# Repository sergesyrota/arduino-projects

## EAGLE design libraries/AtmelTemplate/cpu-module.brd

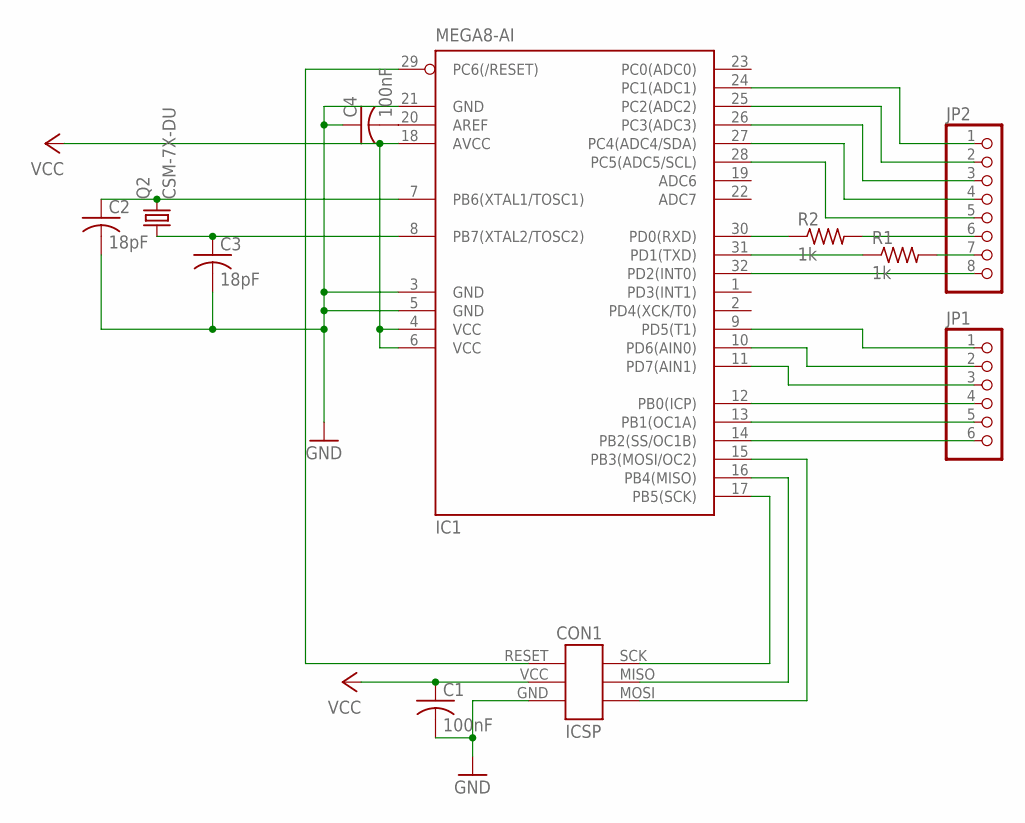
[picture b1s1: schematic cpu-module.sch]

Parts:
C1, C4: 100nF; C0603K
C2, C3: 18pF; C0805
CON1: ICSP-HEADER
IC1: MEGA8-AI; TQFP32-08
JP1: PINHD-1X6B; 1X06-BIG
JP2: PINHD-1X8BIG; 1X08-BIG
Q2: CSM-7X-DU
R1, R2: 1k; R0603

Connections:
GND: C1.2, C2.2, C3.2, C4.1, CON1.GND, IC1.3 (GND), IC1.5 (GND), IC1.21 (GND)
unnamed: C2.1, IC1.7 (PB6(XTAL1/TOSC1)), Q2.2
unnamed: C3.1, IC1.8 (PB7(XTAL2/TOSC2)), Q2.1
unnamed: C4.2, IC1.20 (AREF)
unnamed: CON1.SCK, IC1.17 (PB5(SCK))
unnamed: CON1.MISO, IC1.16 (PB4(MISO))
unnamed: CON1.MOSI, IC1.15 (PB3(MOSI/OC2))
unnamed: IC1.30 (PD0(RXD)), R2.1
unnamed: JP2.7, R1.2
unnamed: IC1.31 (PD1(TXD)), R1.1
unnamed: IC1.32 (PD2(INT0)), JP2.8
unnamed: IC1.24 (PC1(ADC1)), JP2.1
unnamed: CON1.RESET, IC1.29 (PC6(/RESET))
unnamed: IC1.25 (PC2(ADC2)), JP2.2
unnamed: IC1.26 (PC3(ADC3)), JP2.3
unnamed: IC1.27 (PC4(ADC4/SDA)), JP2.4
unnamed: IC1.28 (PC5(ADC5/SCL)), JP2.5
unnamed: IC1.14 (PB2(SS/OC1B)), JP1.6
unnamed: IC1.13 (PB1(OC1A)), JP1.5
unnamed: IC1.12 (PB0(ICP)), JP1.4
unnamed: IC1.11 (PD7(AIN1)), JP1.3
unnamed: IC1.10 (PD6(AIN0)), JP1.2
unnamed: IC1.9 (PD5(T1)), JP1.1
unnamed: JP2.6, R2.2
VCC: C1.1, CON1.VCC (+5V), IC1.4 (VCC), IC1.6 (VCC), IC1.18 (AVCC)

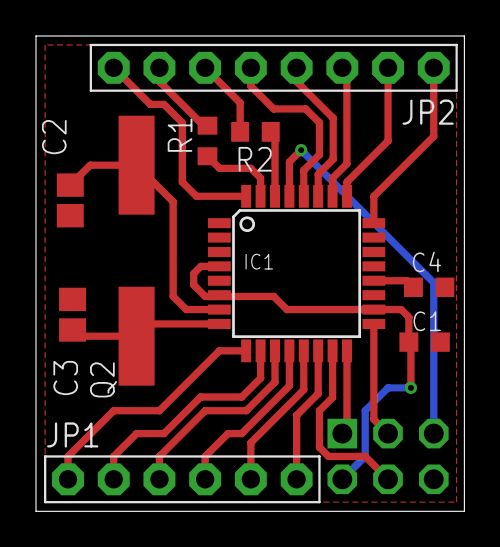
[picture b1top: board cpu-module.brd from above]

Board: 2 copper layers, 23.8 x 26.4 mm, 11 parts (1 on the bottom side), 25 nets.

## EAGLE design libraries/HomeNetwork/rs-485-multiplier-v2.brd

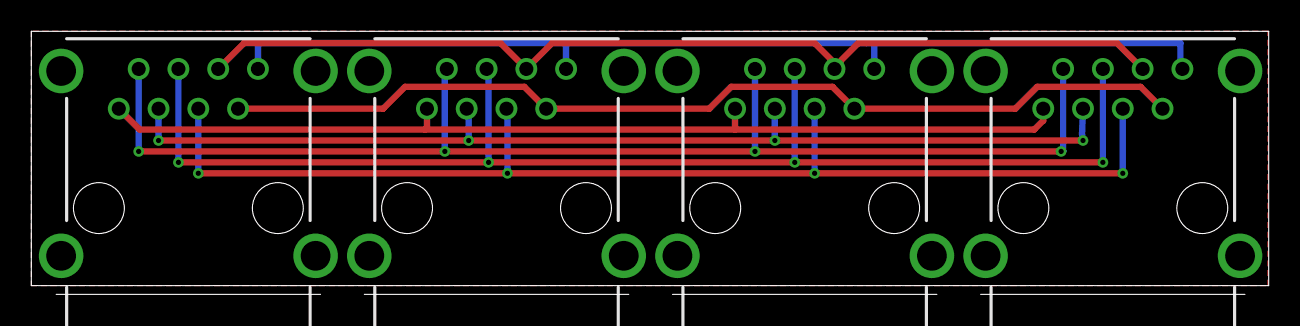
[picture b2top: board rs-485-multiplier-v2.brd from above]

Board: 2 copper layers, 79.0 x 16.8 mm, 4 parts (0 on the bottom side), 8 nets.

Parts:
X1, X2, X3, X4: RJ45-6L21-B; RJ45-SHIELD1

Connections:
unnamed: X1.1, X2.1, X3.1, X4.1
unnamed: X1.2, X2.2, X3.2, X4.2
unnamed: X1.3, X2.3, X3.3, X4.3
unnamed: X1.4, X2.4, X3.4, X4.4
unnamed: X1.5, X2.5, X3.5, X4.5
unnamed: X1.6, X2.6, X3.6, X4.6
unnamed: X1.7, X2.7, X3.7, X4.7
unnamed: X1.8, X2.8, X3.8, X4.8

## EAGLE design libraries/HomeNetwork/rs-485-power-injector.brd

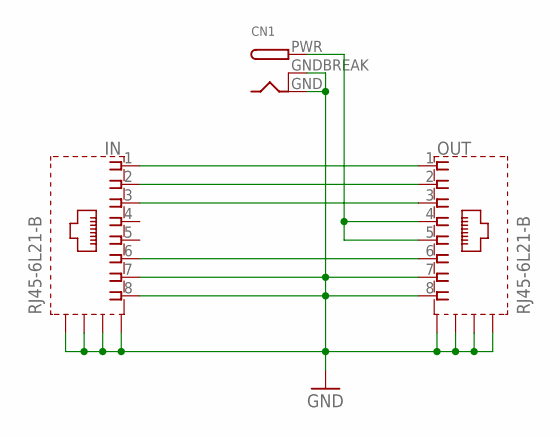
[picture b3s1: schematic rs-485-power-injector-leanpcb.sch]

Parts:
CN1: DCBARRELPTH; DCJACK_2MM_PTH
IN: RJ45-6L21-B; RJ45-SHIELD1
OUT: RJ45-6L21-B; RJ45-SHIELD1

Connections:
GND: CN1.GND, CN1.GNDBREAK, IN.7, IN.8, IN.S1 (S), IN.S2 (S), IN.S3 (S), IN.S4 (S), OUT.7, OUT.8, OUT.S1 (S), OUT.S2 (S), OUT.S3 (S), OUT.S4 (S)
unnamed: IN.1, OUT.1
unnamed: IN.2, OUT.2
unnamed: IN.3, OUT.3
unnamed: IN.6, OUT.6
unnamed: CN1.PWR, OUT.4, OUT.5

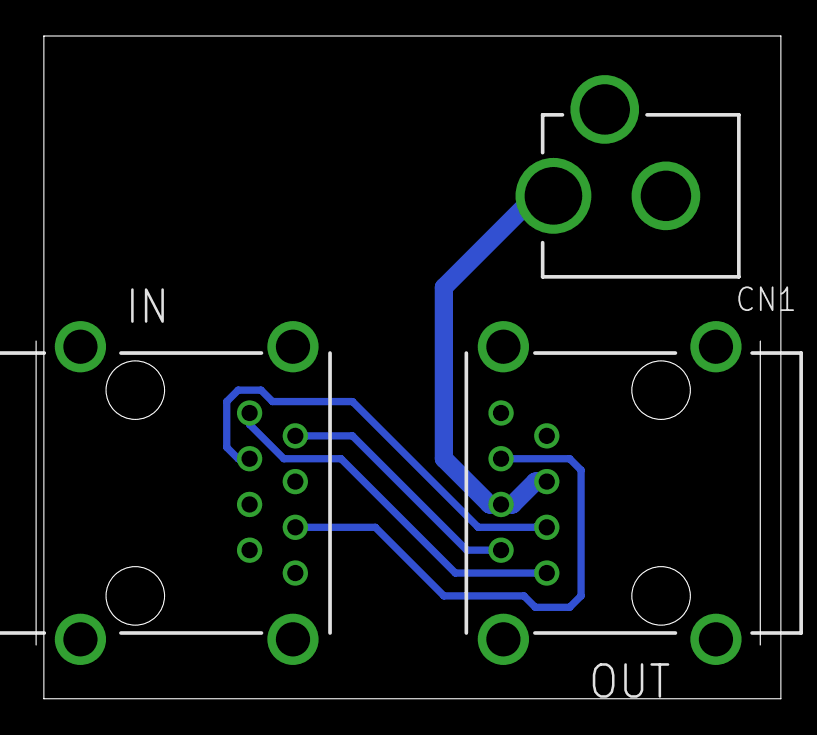
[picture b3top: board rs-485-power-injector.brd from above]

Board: 2 copper layers, 40.9 x 36.8 mm, 3 parts (0 on the bottom side), 6 nets.

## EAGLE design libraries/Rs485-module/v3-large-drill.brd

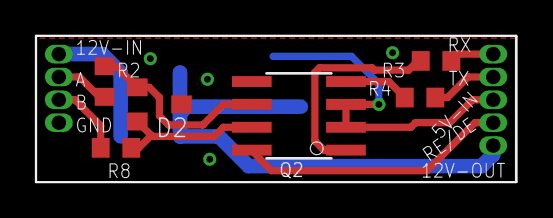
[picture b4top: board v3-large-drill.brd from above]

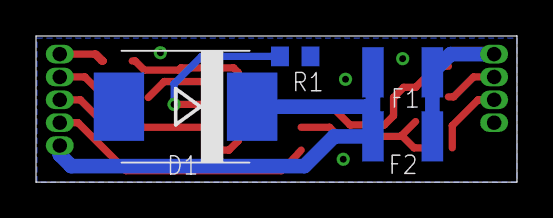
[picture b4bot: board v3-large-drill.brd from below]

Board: 2 copper layers, 26.7 x 8.1 mm, 11 parts (4 on the bottom side), 13 nets.

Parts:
D1: SMC
D2: SM712SOT23-3-SHRINKED; SOT23-3-SHRINKED
F1, F2: PTC-1210; 1210
Q1: RS485-ADAPTER0.05-CONNECTOR; RS485-ADAPTOR-05
Q2: MAX481SO08; SO08
R1: 50k; R0603
R2, R8: 100; R0603
R3, R4: 1k; R0603

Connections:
12V-IN: F1.2, F2.2, Q1.12V-IN
A: Q1.A, R2.2
B: Q1.B, R8.2
GND: D1.A, D2.3, Q1.GND, Q2.5, R1.1
unnamed: D2.2, Q2.7, R8.1
unnamed: Q2.1, R3.2
unnamed: Q2.4, R4.2
unnamed: D2.1, Q2.6, R2.1
RE/DE: Q1.RE/DE, Q2.2, Q2.3, R1.2
RX: Q1.RX, R3.1
TX: Q1.TX, R4.1
V+: D1.C, F1.1, F2.1, Q1.12V-OUT
VCC: Q1.5V-IN, Q2.8

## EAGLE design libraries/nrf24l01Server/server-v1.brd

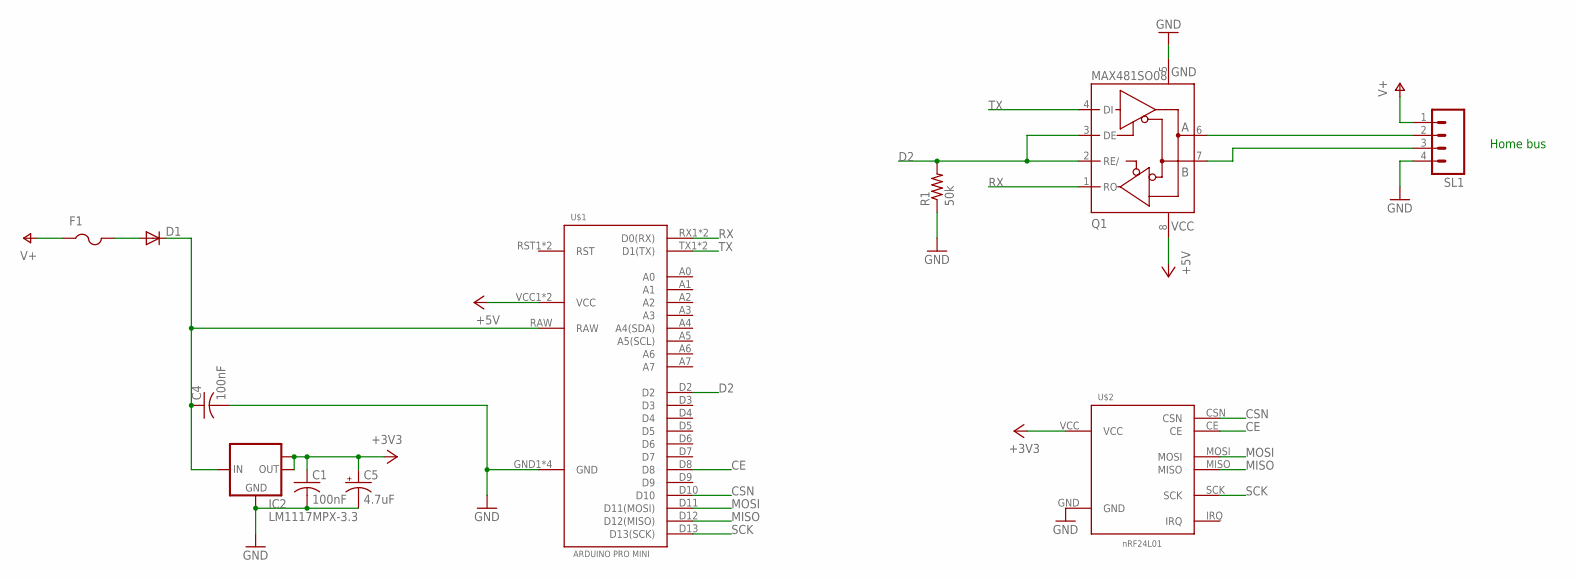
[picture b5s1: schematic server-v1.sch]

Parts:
C1, C4: 100nF; C0603K
C5: 4.7uF; E1,8-4
D1: DIODE-MICROMELF-W; MICROMELF-W
F1: PTCFUSE-1812; 1812
IC2: LM1117MPX-3.3; SOT223
Q1: MAX481SO08; SO08
R1: 50k; R0603
SL1: M04; 04P
U$1: ARDUINO-PRO-MINI
U$2: NRF24L01MODULE; NRF24L01-MODULE

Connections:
+3V3: C1.1, C5.+, IC2.2 (OUT), IC2.TAB (OUT1), U$2.VCC
+5V: Q1.8 (+5V), U$1.VCC1 (VCC), U$1.VCC2 (VCC)
+12V: C4.1, D1.C, IC2.3 (IN), U$1.RAW
CE: U$1.D8, U$2.CE
CSN: U$1.D10, U$2.CSN
D2: Q1.2 (RE/), Q1.3 (DE), R1.2, U$1.D2
GND: C1.2, C4.2, C5.-, IC2.1 (GND), Q1.5 (GND), R1.1, SL1.4, U$1.GND1 (GND), U$1.GND2 (GND), U$1.GND3 (GND), U$1.GND4 (GND), U$2.GND
MISO: U$1.D12 (D12(MISO)), U$2.MISO
MOSI: U$1.D11 (D11(MOSI)), U$2.MOSI
unnamed: D1.A, F1.2
unnamed: Q1.6 (A), SL1.2
unnamed: Q1.7 (B), SL1.3
RX: Q1.1 (RO), U$1.RX1 (D0(RX)), U$1.RX2 (D0(RX))
SCK: U$1.D13 (D13(SCK)), U$2.SCK
TX: Q1.4 (DI), U$1.TX1 (D1(TX)), U$1.TX2 (D1(TX))
V+: F1.1, SL1.1

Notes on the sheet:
Home bus

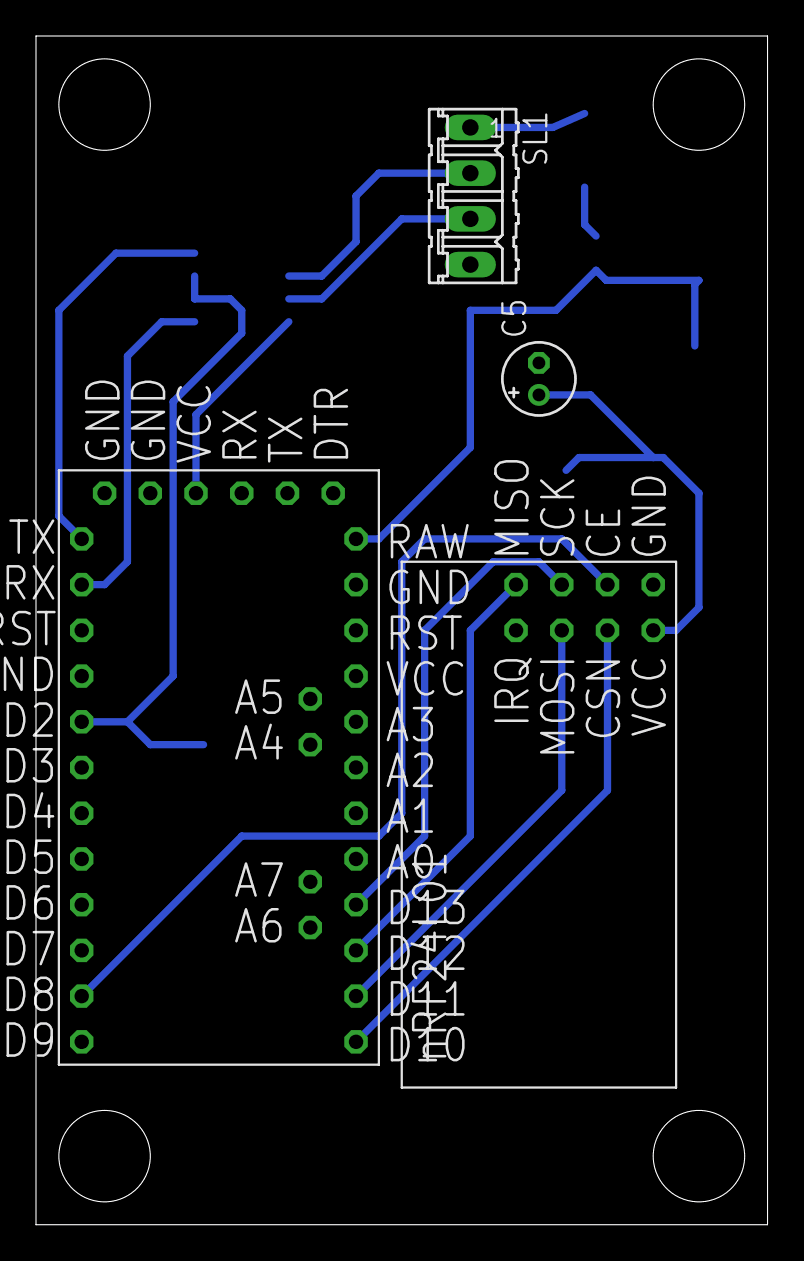
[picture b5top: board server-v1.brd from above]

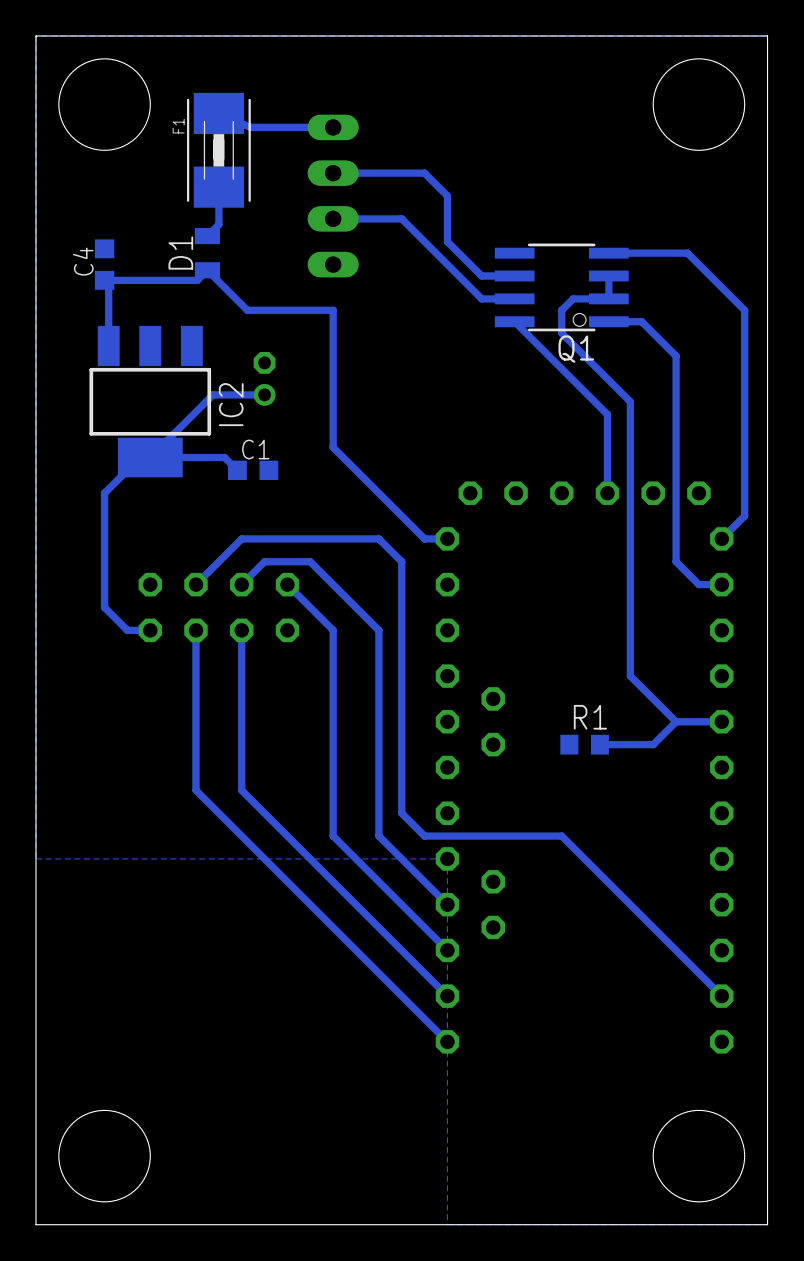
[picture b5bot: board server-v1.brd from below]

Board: 2 copper layers, 40.6 x 66.0 mm, 11 parts (7 on the bottom side), 16 nets.

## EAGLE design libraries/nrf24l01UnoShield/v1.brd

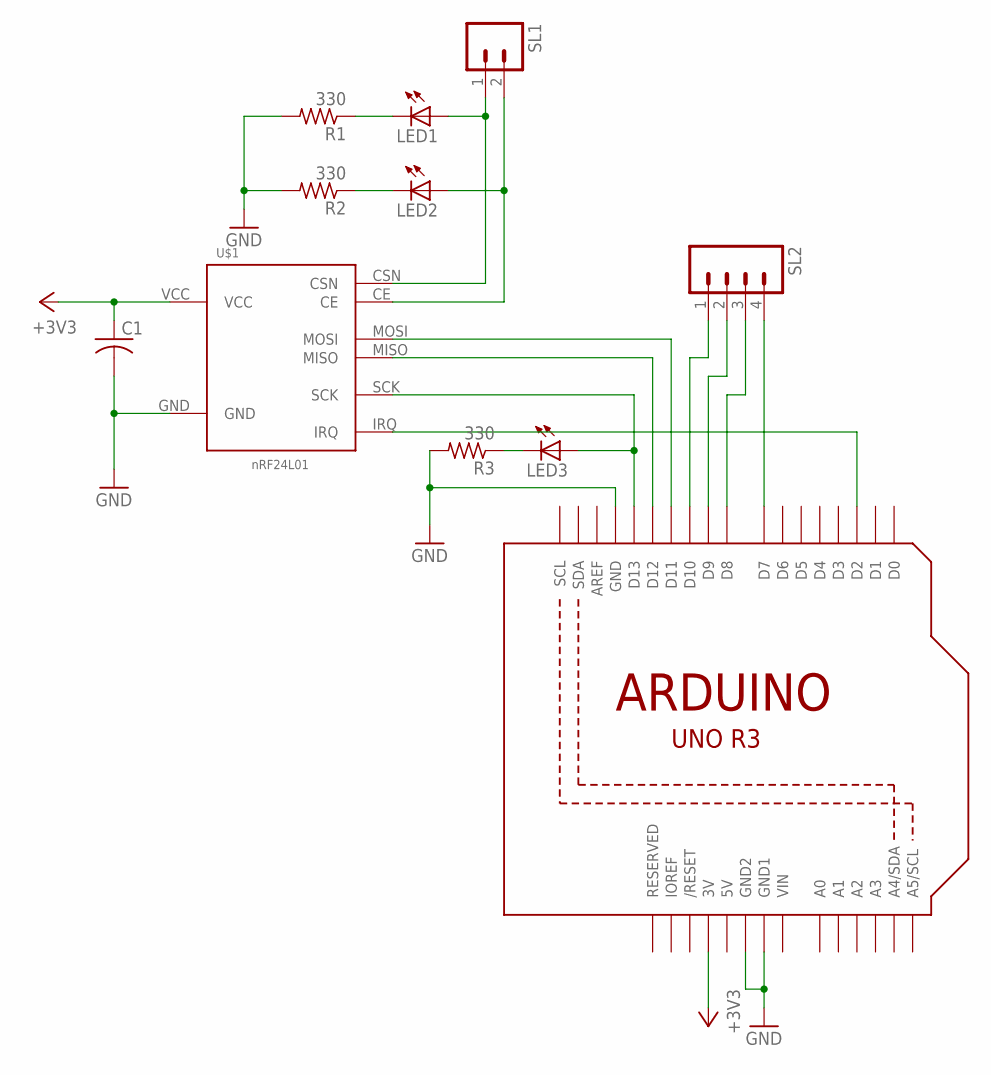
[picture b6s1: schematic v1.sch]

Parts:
C1: C-USC0603; C0603
LED1, LED2, LED3: LED5MM
R1, R2, R3: 330; R0603
SL1: M02; 02P
SL2: M04; 04P
U1: ARDUINOR3-DIMENSION; ARDUINOR3
U$1: NRF24L01MODULE; NRF24L01-MODULE

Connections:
5V: U1.5V
+3V3: C1.1, U1.3V, U$1.VCC
GND: C1.2, R1.2, R2.2, R3.2, U1.GND, U1.GND1, U1.GND2, U$1.GND
unnamed: SL2.4, U1.D7
unnamed: SL2.3, U1.D8
unnamed: LED3.A, U1.D13, U$1.SCK
unnamed: U1.D12, U$1.MISO
unnamed: U1.D11, U$1.MOSI
unnamed: U1.D2, U$1.IRQ
unnamed: SL2.2, U1.D9
unnamed: SL2.1, U1.D10
unnamed: LED1.A, SL1.1, U$1.CSN
unnamed: LED2.A, SL1.2, U$1.CE
unnamed: LED1.K (C), R1.1
unnamed: LED2.K (C), R2.1
unnamed: LED3.K (C), R3.1
VIN: U1.VIN

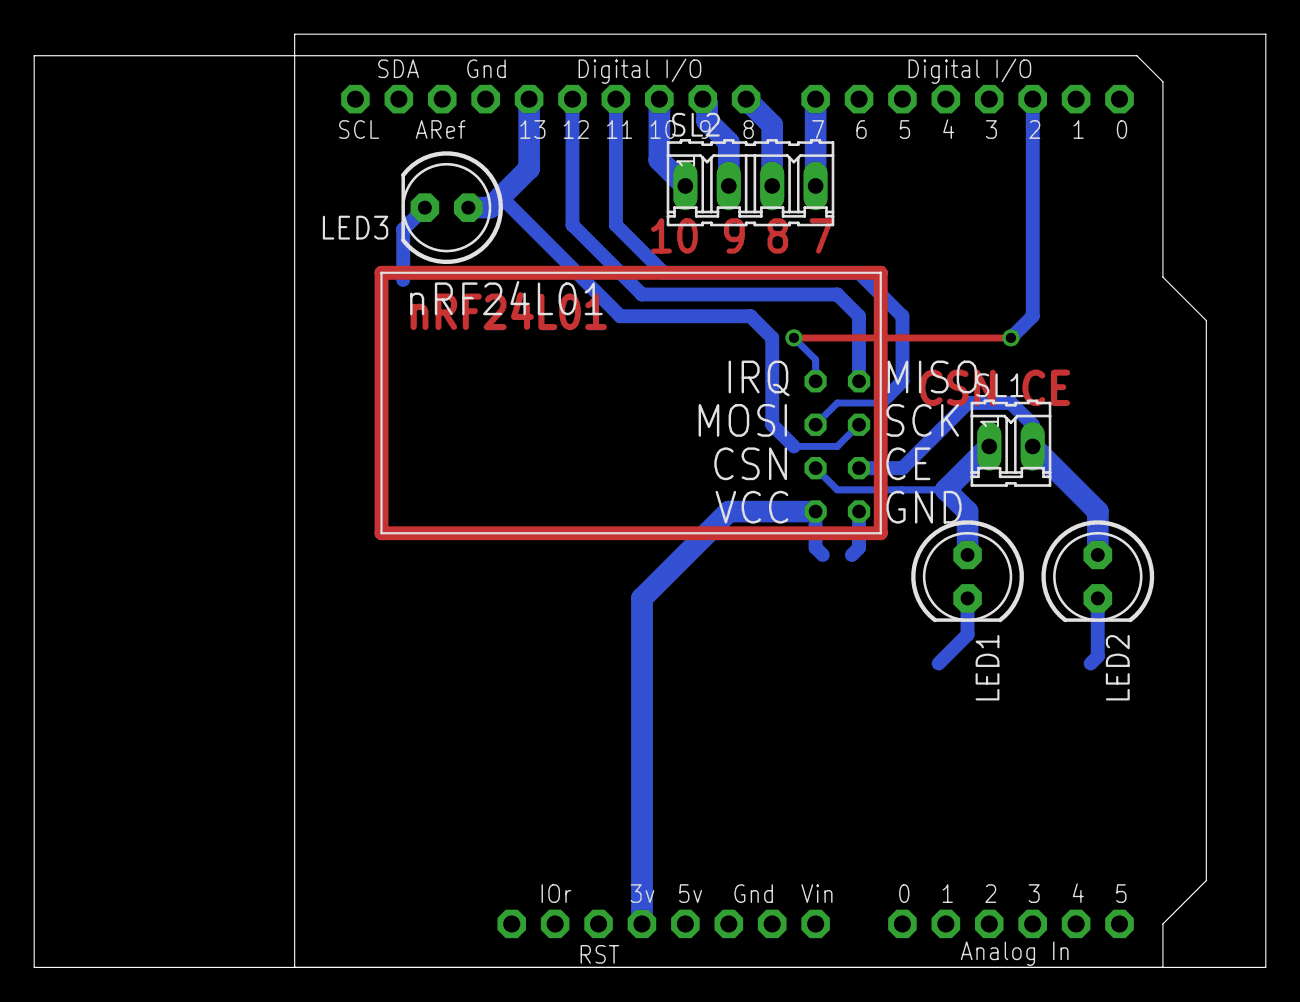
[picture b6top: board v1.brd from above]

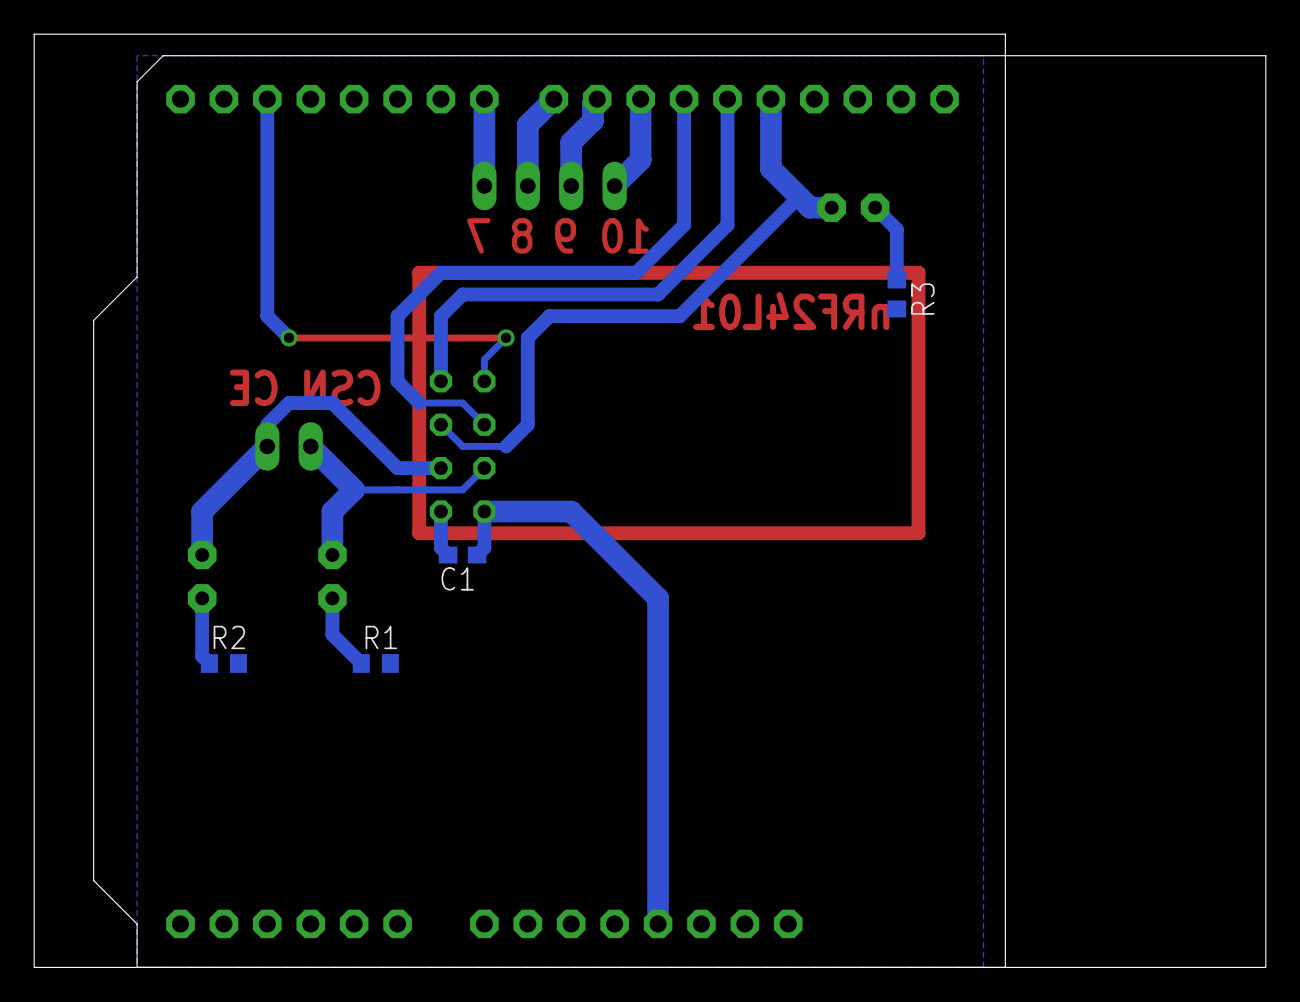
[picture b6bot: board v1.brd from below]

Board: 2 copper layers, 72.1 x 54.6 mm, 11 parts (4 on the bottom side), 15 nets.
